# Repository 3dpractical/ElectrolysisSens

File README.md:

# ElectrolysisSens
Monitoring Electrodes' Reaction on Elecytrolysis Process. Measuring Voltage and Current using INA226 Sensor and pH value of the fluid. Sensor data is transmitted to Web Based on IoT.

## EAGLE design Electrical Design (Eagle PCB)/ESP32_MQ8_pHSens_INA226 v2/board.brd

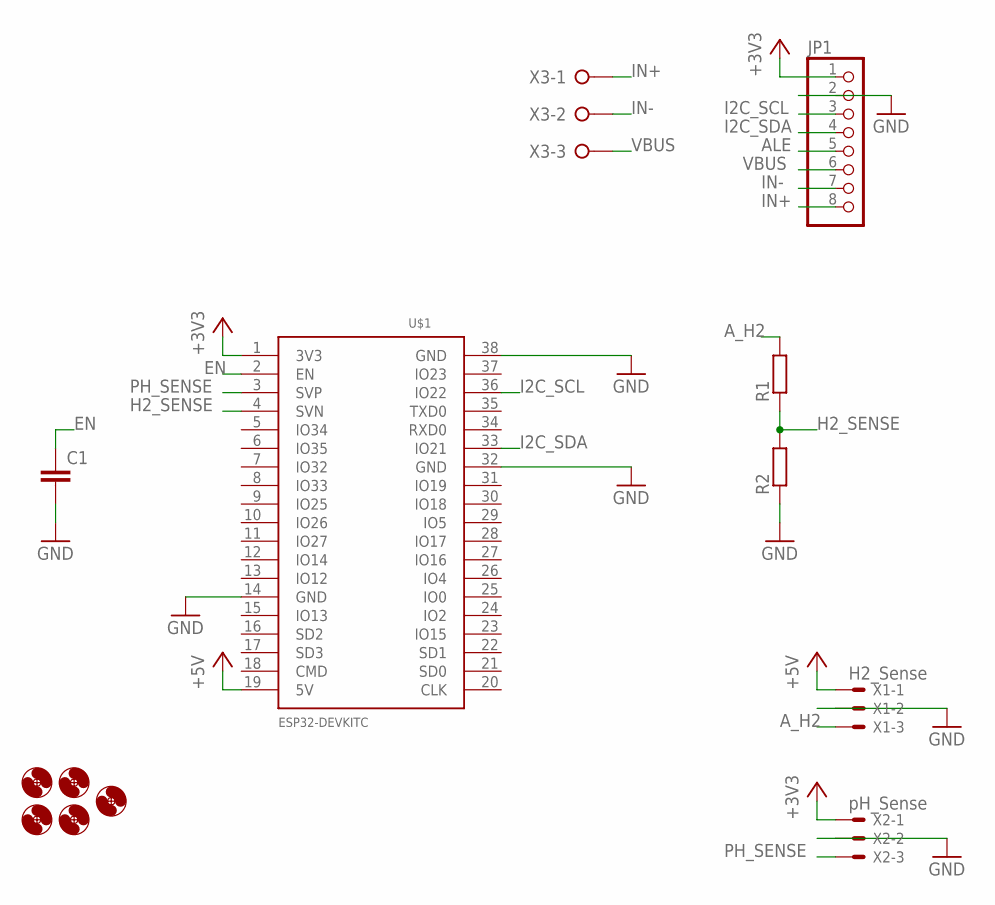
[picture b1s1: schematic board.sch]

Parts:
C1: C-EUC0805; C0805
H1, H2, H3, H4, H6: MOUNT-HOLE3.0; 3,0
JP1: PINHD-1X8; 1X08
R1, R2: R-EU_R0805; R0805
U$1: ESP32DEVKITC; ESP32-DEVKITC
X1: H2_Sense; JST-XH-03-PACKAGE-LONG-PAD
X2: pH_Sense; JST-XH-03-PACKAGE-LONG-PAD
X3: W237-3E

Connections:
+3V3: JP1.1, U$1.1 (3V3), X2.1
+5V: U$1.19 (5V), X1.1
ALE: JP1.5
A_H2: R1.2, X1.3
EN: C1.1, U$1.2 (EN)
GND: C1.2, JP1.2, R2.1, U$1.14 (GND), U$1.32 (GND), U$1.38 (GND), X1.2, X2.2
H2_SENSE: R1.1, R2.2, U$1.4 (SVN)
I2C_SCL: JP1.3, U$1.36 (IO22)
I2C_SDA: JP1.4, U$1.33 (IO21)
IN+: JP1.8, X3.1
IN-: JP1.7, X3.2
PH_SENSE: U$1.3 (SVP), X2.3
VBUS: JP1.6, X3.3

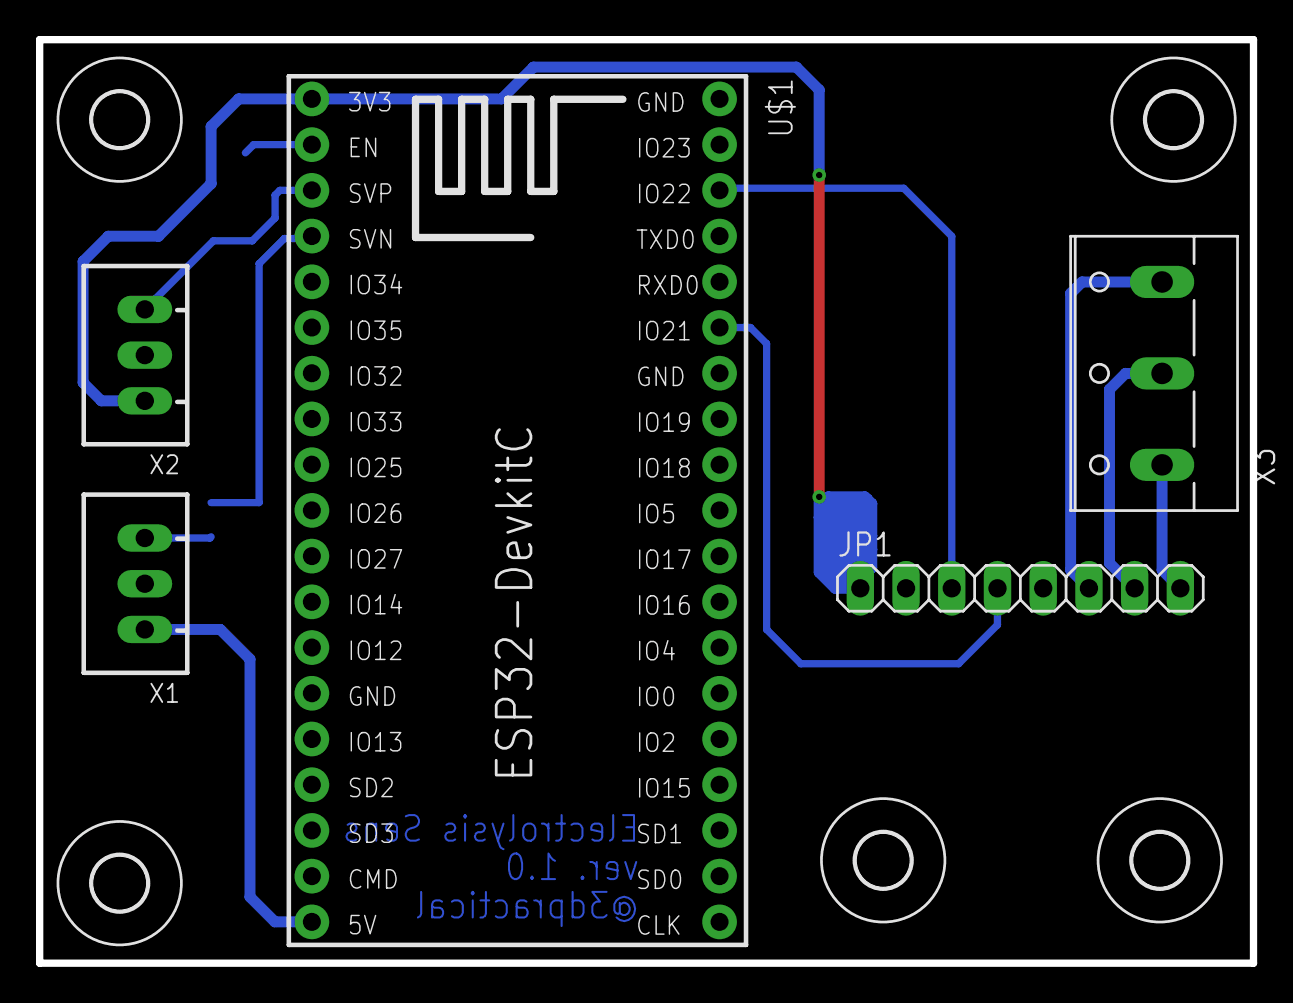
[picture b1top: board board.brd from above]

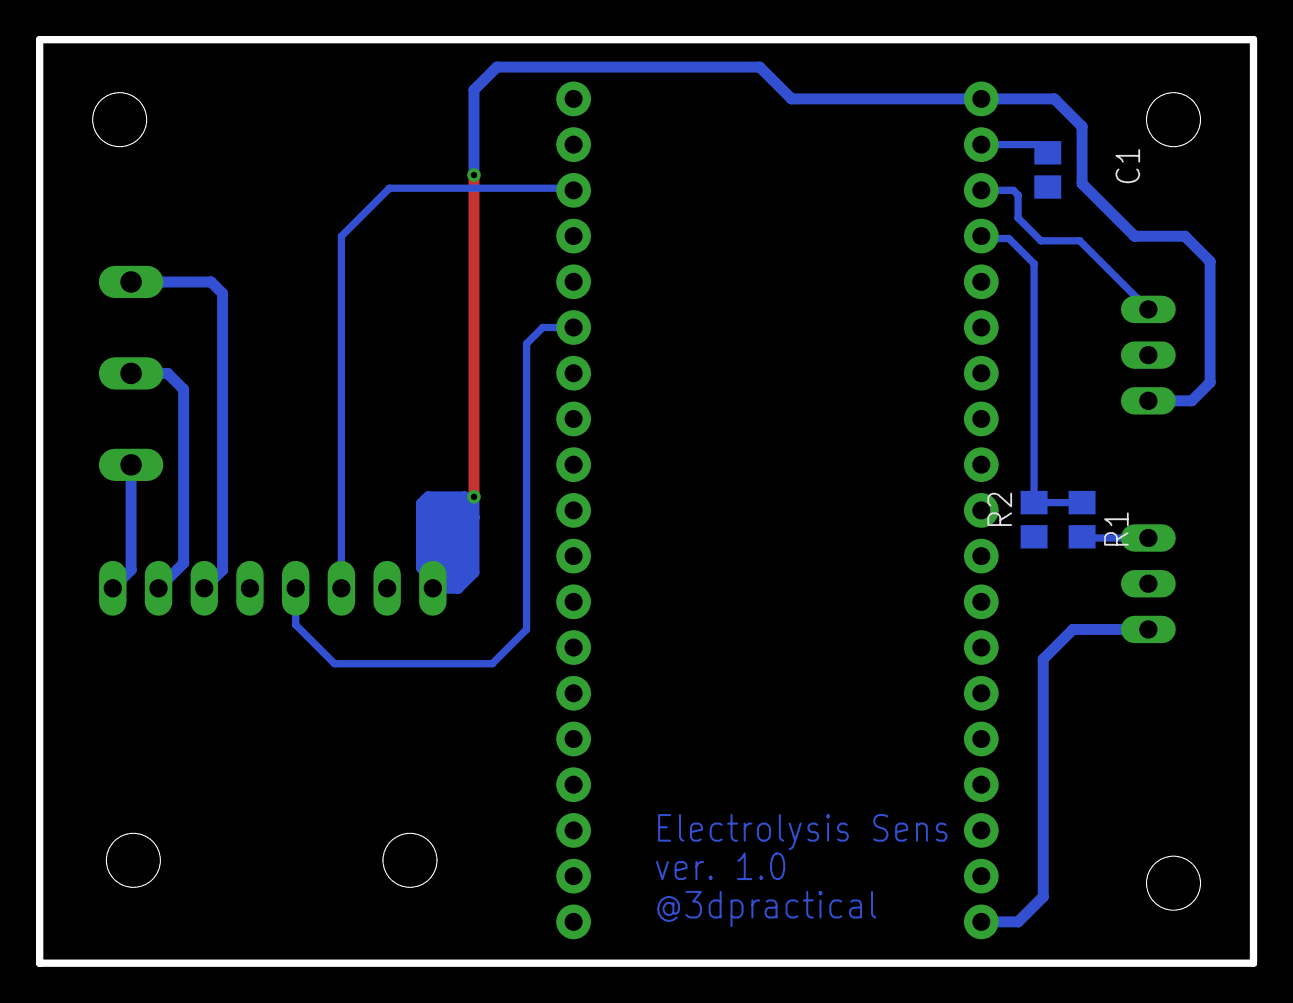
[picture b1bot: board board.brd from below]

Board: 2 copper layers, 67.4 x 51.3 mm, 13 parts (3 on the bottom side), 12 nets.
